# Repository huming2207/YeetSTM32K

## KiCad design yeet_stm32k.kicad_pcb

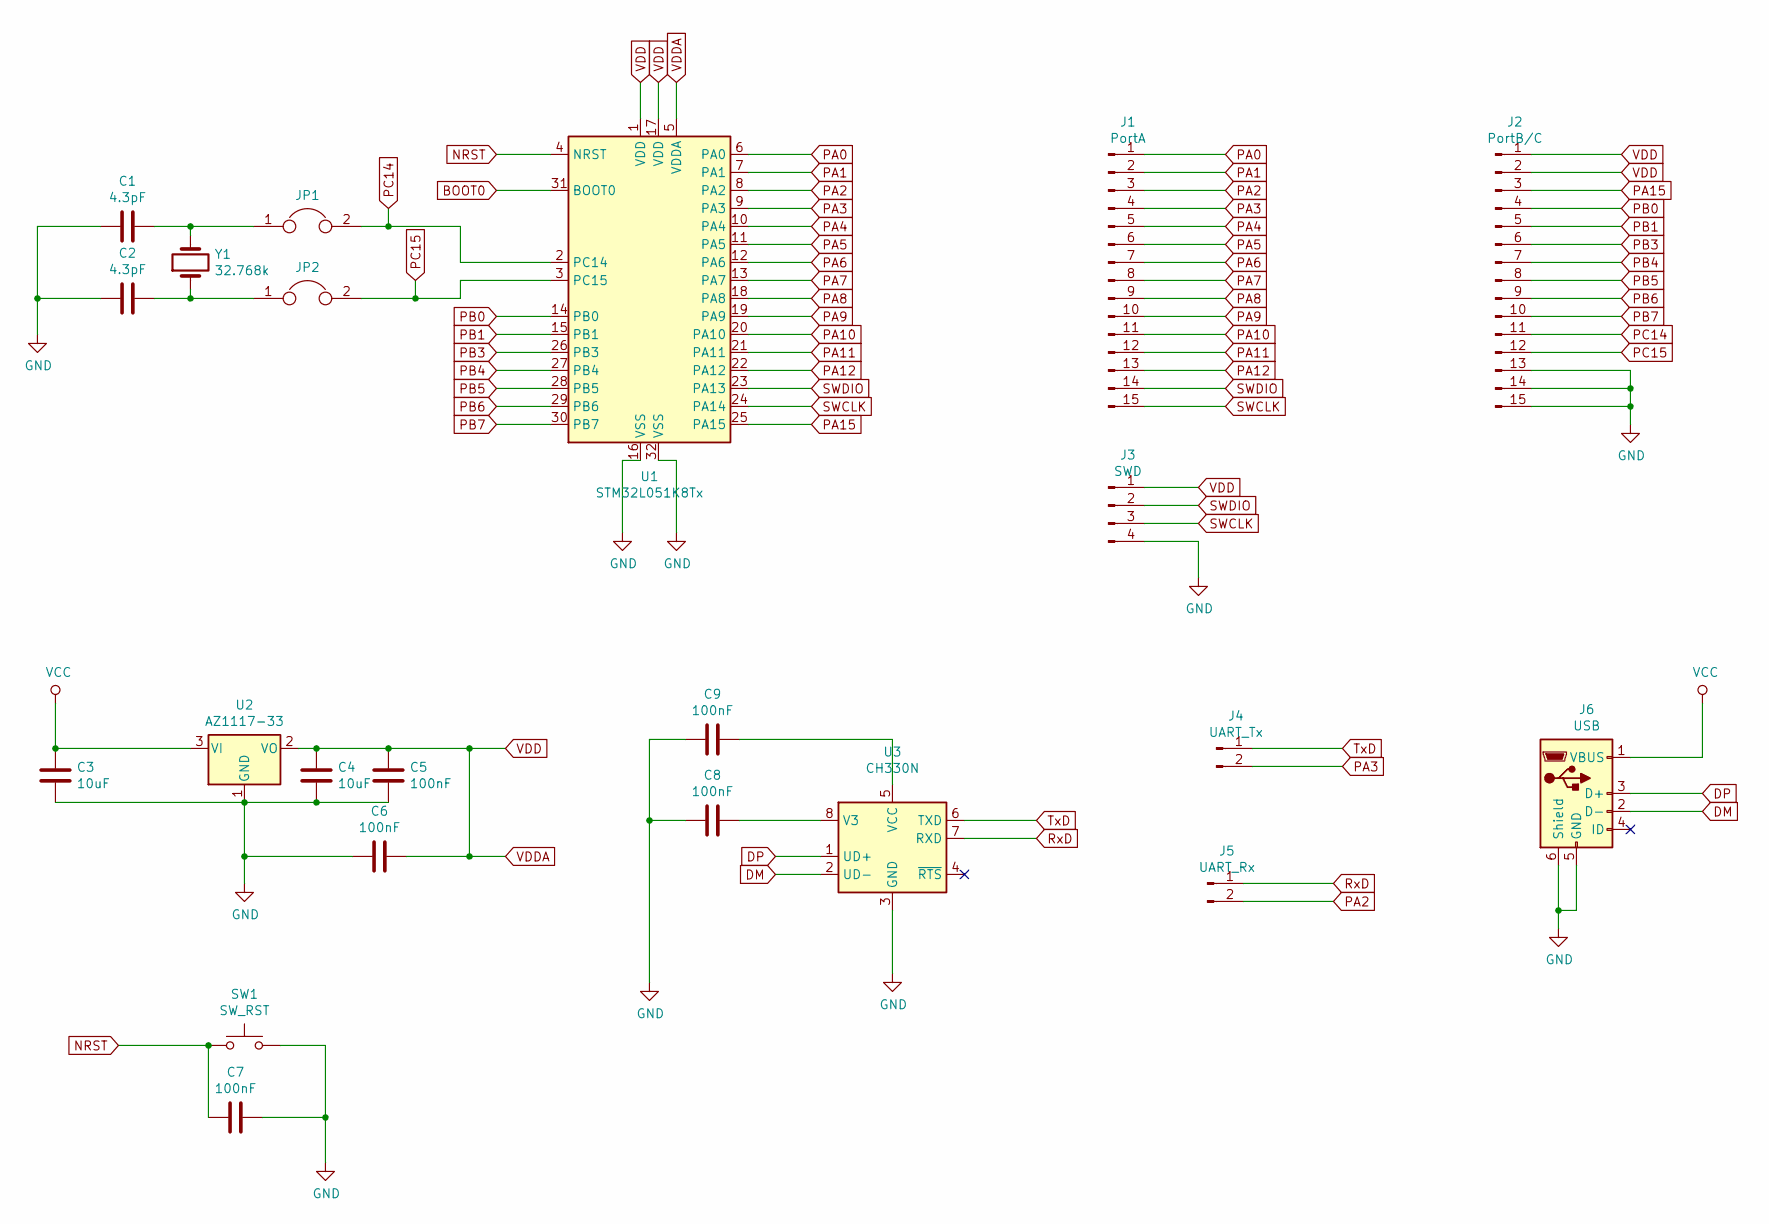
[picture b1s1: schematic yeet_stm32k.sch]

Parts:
C1, C2: 4.3pF; C_0805_2012Metric_Pad1.15x1.40mm_HandSolder
C3, C4: 10uF; C_0805_2012Metric_Pad1.15x1.40mm_HandSolder
C5, C6, C7, C8, C9: 100nF; C_0805_2012Metric_Pad1.15x1.40mm_HandSolder
J1: PortA; PinHeader_1x15_P2.54mm_Vertical
J2: PortB/C; PinHeader_1x15_P2.54mm_Vertical
J3: SWD; PinHeader_1x04_P2.54mm_Vertical
J4: UART_Tx; PinHeader_1x02_P2.54mm_Vertical
J5: UART_Rx; PinHeader_1x02_P2.54mm_Vertical
J6: USB; USB_Micro-B_GCT_USB3076-30-A
JP1, JP2: Jumper; SolderJumper-2_P1.3mm_Open_RoundedPad1.0x1.5mm
SW1: SW_RST; SW_DIP_SPSTx01_Slide_6.7x4.1mm_W8.61mm_P2.54mm_LowProfile
U1: STM32L051K8Tx; LQFP-32_7x7mm_P0.8mm
U2: AZ1117-33; SOT-223-3_TabPin2
U3: CH330N; SOIC-8_3.9x4.9mm_P1.27mm
Y1: 32.768k; Crystal_SMD_EuroQuartz_MJ-4Pin_5.0x3.2mm_HandSoldering

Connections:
BOOT0: U1.31 (BOOT0)
DM: J6.2 (D-), U3.2 (UD-)
DP: J6.3 (D+), U3.1 (UD+)
GND: C1.2, C2.1, C3.2, C4.2, C5.2, C6.2, C7.1, C8.2, C9.2, J2.13, J2.14, J2.15, J3.4, J6.5 (GND), J6.6 (Shield), SW1.2, U1.16 (VSS), U1.32 (VSS), U2.1 (GND), U3.3 (GND)
NRST: C7.2, SW1.1, U1.4 (NRST)
unnamed: C1.1, JP1.1, Y1.2
unnamed: C2.2, JP2.1, Y1.1
unnamed: C8.1, U3.8 (V3)
unnamed: C9.1, U3.5 (VCC)
PA0: J1.1, U1.6 (PA0)
PA1: J1.2, U1.7 (PA1)
PA2: J1.3, J5.2, U1.8 (PA2)
PA3: J1.4, J4.2, U1.9 (PA3)
PA4: J1.5, U1.10 (PA4)
PA5: J1.6, U1.11 (PA5)
PA6: J1.7, U1.12 (PA6)
PA7: J1.8, U1.13 (PA7)
PA8: J1.9, U1.18 (PA8)
PA9: J1.10, U1.19 (PA9)
PA10: J1.11, U1.20 (PA10)
PA11: J1.12, U1.21 (PA11)
PA12: J1.13, U1.22 (PA12)
PA15: J2.3, U1.25 (PA15)
PB0: J2.4, U1.14 (PB0)
PB1: J2.5, U1.15 (PB1)
PB3: J2.6, U1.26 (PB3)
PB4: J2.7, U1.27 (PB4)
PB5: J2.8, U1.28 (PB5)
PB6: J2.9, U1.29 (PB6)
PB7: J2.10, U1.30 (PB7)
PC14: J2.11, JP1.2, U1.2 (PC14)
PC15: J2.12, JP2.2, U1.3 (PC15)
RxD: J5.1, U3.7 (RXD)
SWCLK: J1.15, J3.3, U1.24 (PA14)
SWDIO: J1.14, J3.2, U1.23 (PA13)
TxD: J4.1, U3.6 (TXD)
VCC: C3.1, J6.1 (VBUS), U2.3 (VI)
VDD: C4.1, C5.1, C6.1, J2.1, J2.2, J3.1, U1.1 (VDD), U1.5 (VDDA), U1.17 (VDD), U2.2 (VO)

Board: 2 copper layers, 22 parts (0 on the bottom side), 37 nets, no tracks yet.

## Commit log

2019-10-05 Init
